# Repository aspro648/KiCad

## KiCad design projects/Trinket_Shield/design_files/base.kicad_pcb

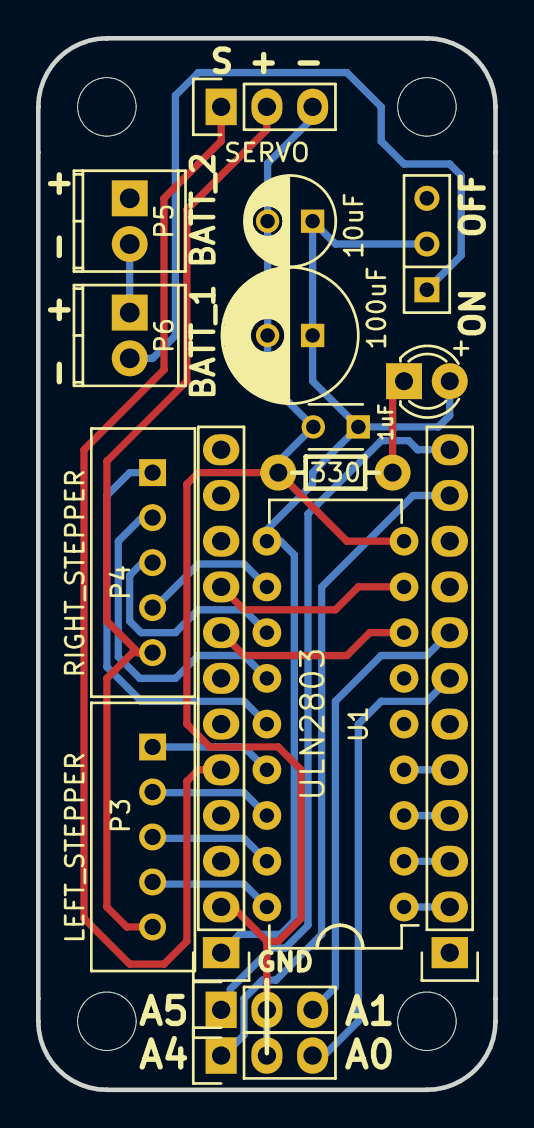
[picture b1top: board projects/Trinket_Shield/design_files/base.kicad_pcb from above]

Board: 2 copper layers, 25.4 x 58.4 mm, 22 parts (0 on the bottom side), 25 nets.

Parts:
C1: 100uF; C_Radial_D7.5_L11.2_P2.5
C2: 10uF; C_Radial_D5_L11_P2.5
C3: 1uF; C_Disc_D3_P2.5
D1: LED; LED-3MM
P1: TRINKET_LEFT; Pin_Header_Straight_1x12
P2: TRINKET_RIGHT; Pin_Header_Straight_1x12
P3: LEFT_STEPPER; JST_B5B-XH-A
P4: RIGHT_STEPPER; JST_B5B-XH-A
P5: BATT1; TerminalBlock_Pheonix_MPT-2.54mm_2pol
P6: BATT2; TerminalBlock_Pheonix_MPT-2.54mm_2pol
P7: SERVO; Pin_Header_Straight_1x03
P8: A5 - A1; Pin_Header_Straight_1x03
P9, P9#2, P9#3, P9#4: CONN_01X01; Lego_Pad
P11: A4 - A0; Pin_Header_Straight_1x03
R1: 330; Resistor_Horz
SW1: SPST; SW_Micro_SPST
U1: ULN2803; DIP-18_W7.62mm
VAL: MadeInOregonRev25
VAL#2: MB225rev

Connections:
/A0: P1.7, P11.3
/A1: P1.8, P8.3
/A4: P1.11, P11.1
/A5: P1.12, P8.1
/D3: P2.9, U1.8
/D4: P2.8, U1.7
/D8: P2.5, P7.1
/D10: P1.2, U1.1
/D11: P1.3, U1.2
/D12: P1.4, U1.3
/D13: P1.5, U1.4
/VBAT: C1.1, C2.1, C3.1, D1.2, P2.1, SW1.2, U1.10
GND: C1.2, C2.2, C3.2, P2.2, P7.3, P8.2, P11.2, R1.2, U1.9
unnamed: D1.1, R1.1
unnamed: P3.1, U1.15
unnamed: P3.2, U1.16
unnamed: P3.3, U1.17
unnamed: P3.4, U1.18
unnamed: P3.5, P4.5, P7.2
unnamed: P4.1, U1.14
unnamed: P4.2, U1.13
unnamed: P4.3, U1.12
unnamed: P4.4, U1.11
unnamed: P5.2, P6.1
unnamed: P6.2, SW1.1

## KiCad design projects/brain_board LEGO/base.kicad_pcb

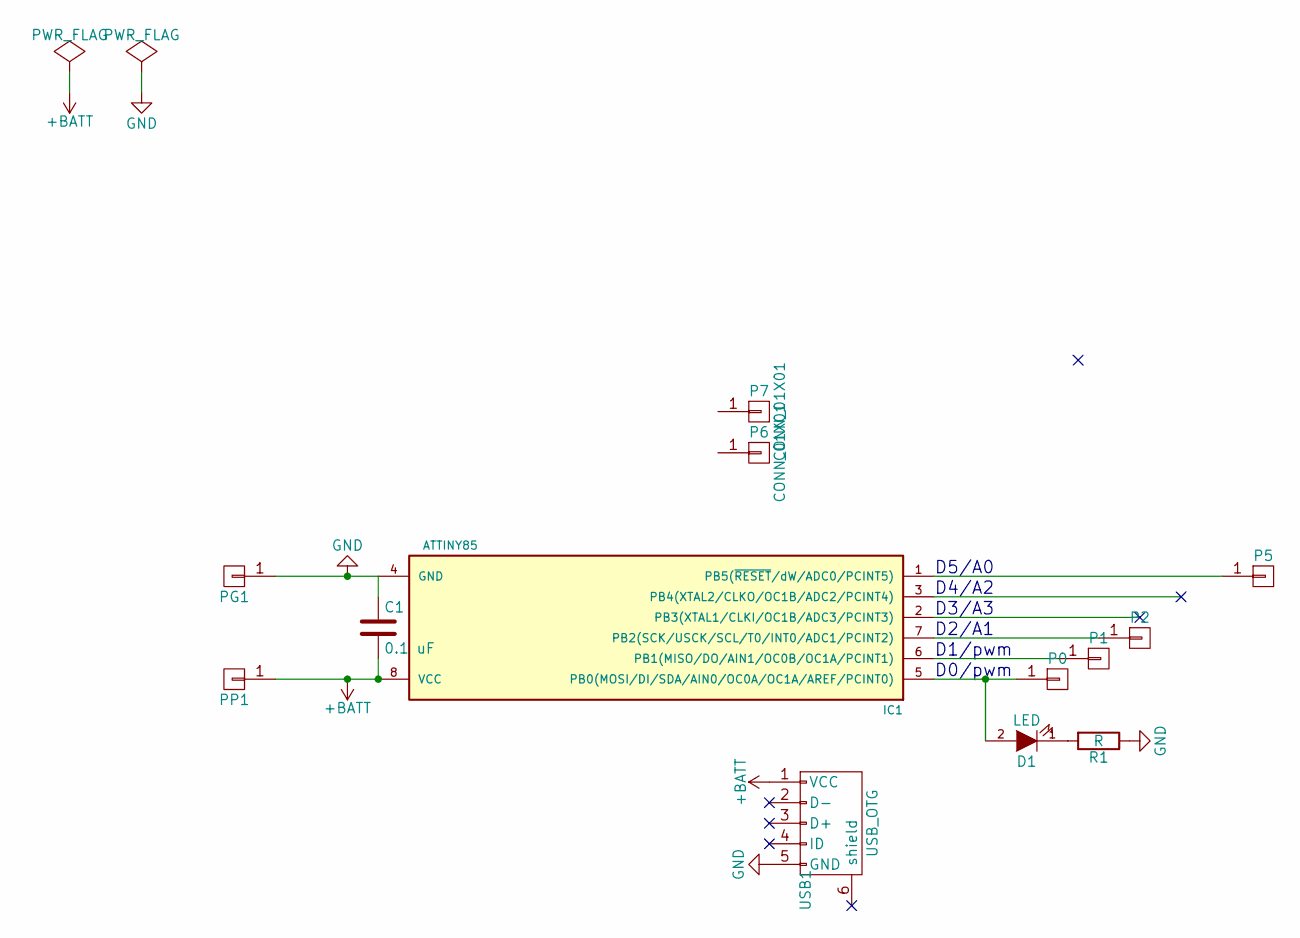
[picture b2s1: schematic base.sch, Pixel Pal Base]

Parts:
C1: 0.1 uF; C_0805
D1: LED; LED-0805
IC1: ATTINY85; SOIC-8-N
P0, P1, P2, P5: CONN_01X01; Lego_Pad
P6, P7: CONN_01X01; Lego_Drill
PG1: CONN_01X01; Lego_Pad
PP1: CONN_01X01; Lego_Pad
R1: R; R_0805
USB1: USB_OTG; USB_Micro-B

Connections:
+BATT: C1.2, IC1.8 (VCC), PP1.1, USB1.1 (VCC)
GND: C1.1, IC1.4 (GND), PG1.1, R1.1, USB1.5 (GND)
unnamed: D1.1 (K), R1.2
unnamed: D1.2 (A), IC1.5 (PB0(MOSI/DI/SDA/AIN0/OC0A/OC1A/AREF/PCI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), P0.1
unnamed: IC1.1 (PB5(~RESET~/dW/ADC0/PCINT5)), P5.1
unnamed: IC1.6 (PB1(MISO/DO/AIN1/OC0B/OC1A/PCINT1)), P1.1
unnamed: IC1.7 (PB2(SCK/USCK/SCL/T0/INT0/ADC1/PCINT2)), P2.1

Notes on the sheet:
D5/A0
D4/A2
D3/A3
D2/A1
D1/pwm
D0/pwm

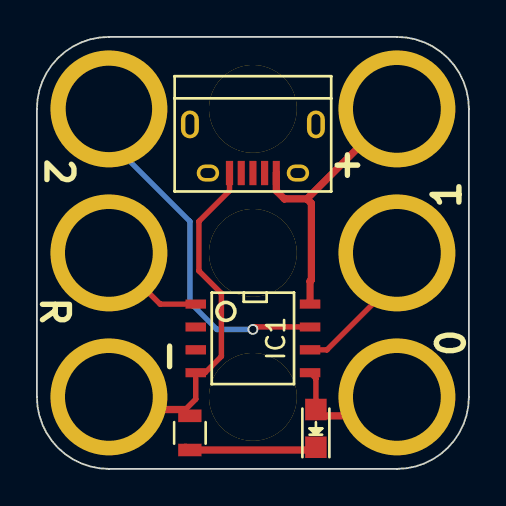
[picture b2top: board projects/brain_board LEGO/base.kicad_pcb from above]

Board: 2 copper layers, 24.0 x 24.0 mm, 13 parts (0 on the bottom side), 7 nets.

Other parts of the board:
P6#2: CONN_01X01; Lego_Drill

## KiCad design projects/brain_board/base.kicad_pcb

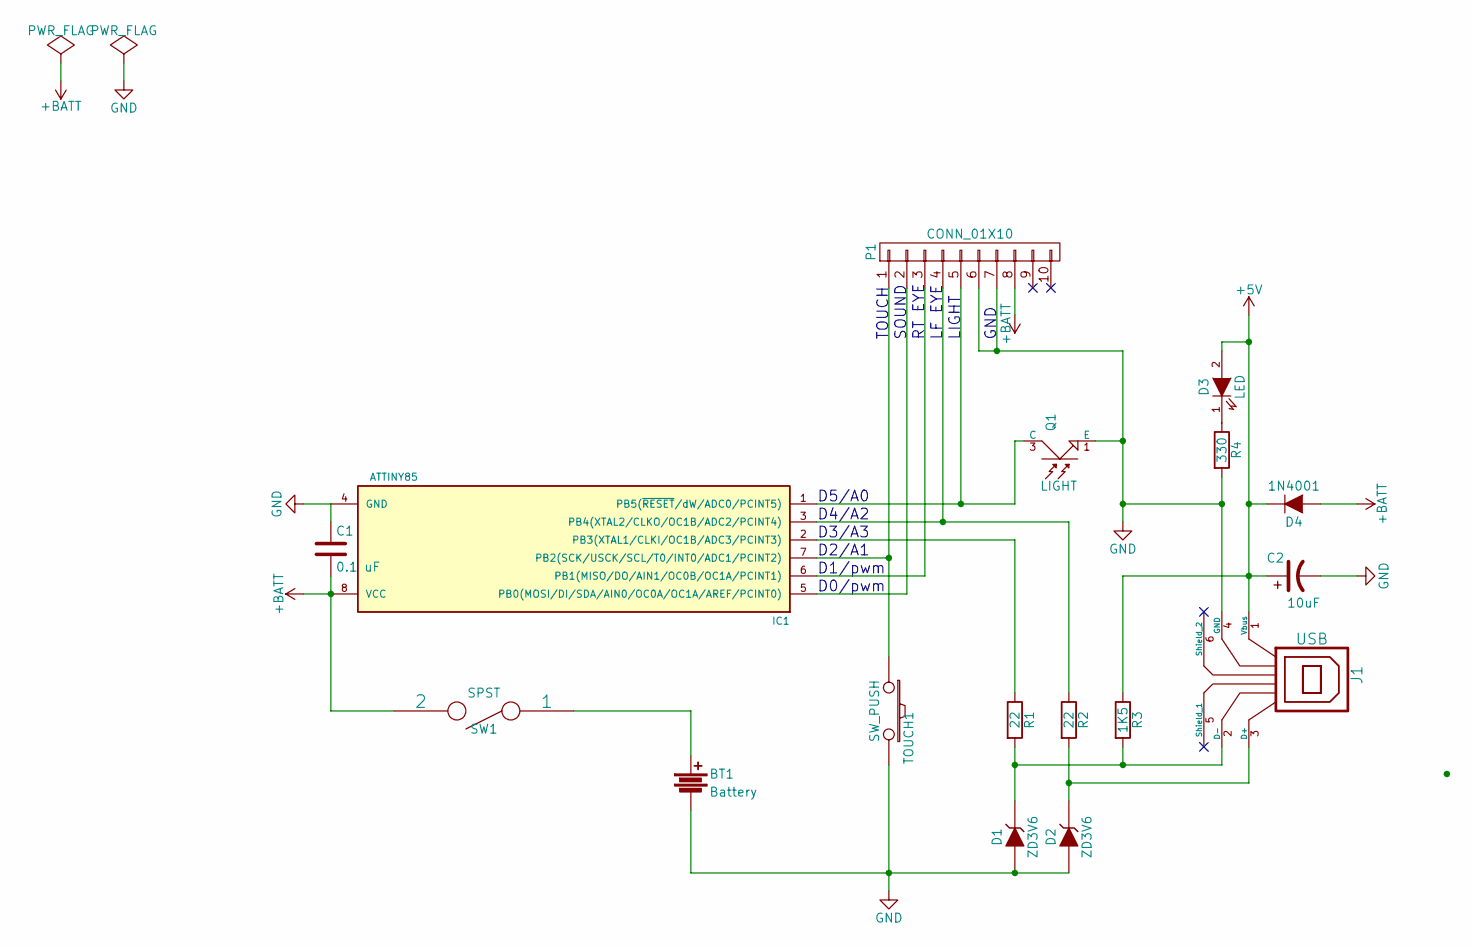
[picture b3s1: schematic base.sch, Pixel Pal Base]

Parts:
BT1: Battery; BATT_CR2032
C1: 0.1 uF; C1
C2: 10uF; C_Radial_D6.3_L11.2_P2.5
D1, D2: ZD3V6; D3
D3: LED; LED-5MM
D4: 1N4001; Diode_DO-41_SOD81_Horizontal_RM10
IC1: ATTINY85; DIP-8__300
J1: USB; USB_B
P1: CONN_01X10; Pin_Header_Straight_1x10
Q1: LIGHT; PHOTO_TRANS
R1, R2: 22; Resistor_Horizontal_RM10mm
R3: 1K5; Resistor_Horizontal_RM10mm
R4: 330; Resistor_Horizontal_RM10mm
SW1: SPST; SW_SPST
TOUCH1: SW_PUSH; SW_PUSH_TOUCH

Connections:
+5V: C2.1, D3.2 (A), D4.2 (K), J1.1 (Vbus), R3.1
+BATT: C1.2, D4.1 (A), IC1.8 (VCC), P1.8, SW1.2
GND: BT1.2, C1.1, C2.2, D1.1 (A), D2.1 (A), IC1.4 (GND), J1.4 (GND), P1.6, P1.7, Q1.1 (E), R4.2, TOUCH1.2
unnamed: BT1.1, SW1.1
unnamed: D1.2 (K), J1.2 (D-), R1.2, R3.2
unnamed: D2.2 (K), J1.3 (D+), R2.2
unnamed: D3.1 (K), R4.1
unnamed: IC1.1 (PB5(~RESET~/dW/ADC0/PCINT5)), P1.5, Q1.3 (C)
unnamed: IC1.2 (PB3(XTAL1/CLKI/OC1B/ADC3/PCINT3)), R1.1
unnamed: IC1.3 (PB4(XTAL2/CLKO/OC1B/ADC2/PCINT4)), P1.4, R2.1
unnamed: IC1.5 (PB0(MOSI/DI/SDA/AIN0/OC0A/OC1A/AREF/PCI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), P1.2
unnamed: IC1.6 (PB1(MISO/DO/AIN1/OC0B/OC1A/PCINT1)), P1.3
unnamed: IC1.7 (PB2(SCK/USCK/SCL/T0/INT0/ADC1/PCINT2)), P1.1, TOUCH1.1

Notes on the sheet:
D5/A0
D4/A2
D3/A3
D2/A1
D1/pwm
D0/pwm
TOUCH
SOUND
RT EYE
LF EYE
GND
LIGHT

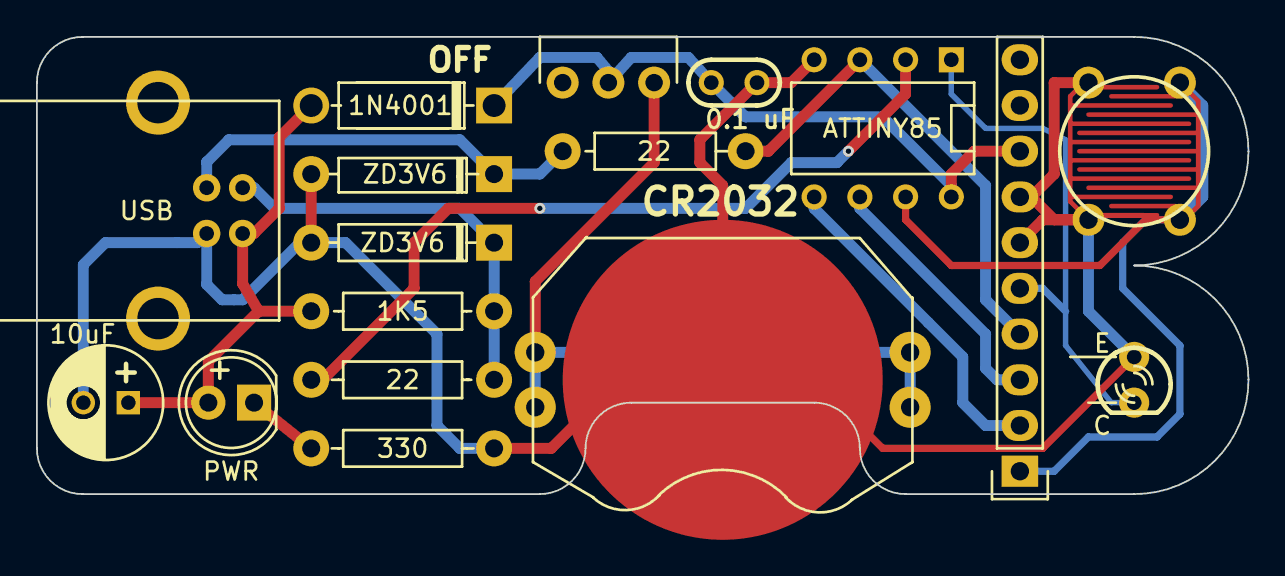
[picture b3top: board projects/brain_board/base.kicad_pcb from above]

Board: 2 copper layers, 67.3 x 25.4 mm, 17 parts (0 on the bottom side), 13 nets.

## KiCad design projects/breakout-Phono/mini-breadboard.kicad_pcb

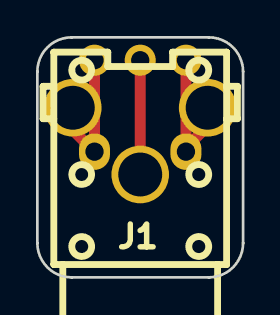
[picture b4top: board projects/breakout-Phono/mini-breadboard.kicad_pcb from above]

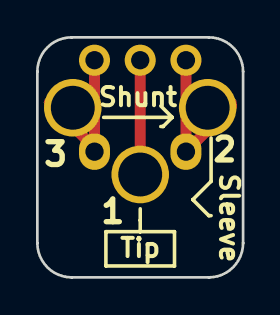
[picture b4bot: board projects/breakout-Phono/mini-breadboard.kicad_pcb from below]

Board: 2 copper layers, 11.4 x 13.3 mm, 3 parts (2 on the bottom side), 3 nets.

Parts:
J1: JACK_2P; rca_yellow
P1, P2: CONN_01X03; Pin_Header_Straight_1x03

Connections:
unnamed: J1.1, P1.1, P2.1
unnamed: J1.2, P1.2
unnamed: J1.3, P1.3, P2.3

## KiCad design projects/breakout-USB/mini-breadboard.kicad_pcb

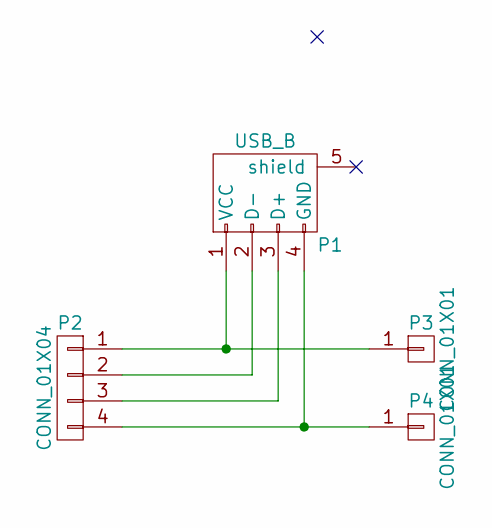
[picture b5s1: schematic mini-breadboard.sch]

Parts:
P1: USB_B
P2: CONN_01X04; Pin_Header_Straight_1x04
P3, P4: CONN_01X01; Pin_Header_Straight_1x01

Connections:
unnamed: P1.1 (VCC), P2.1, P3.1
unnamed: P1.2 (D-), P2.2
unnamed: P1.3 (D+), P2.3
unnamed: P1.4 (GND), P2.4, P4.1

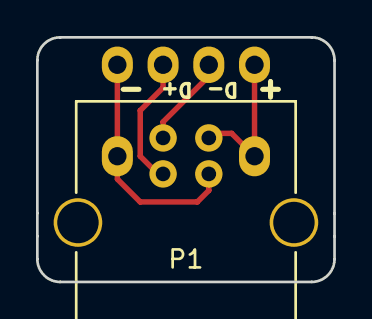
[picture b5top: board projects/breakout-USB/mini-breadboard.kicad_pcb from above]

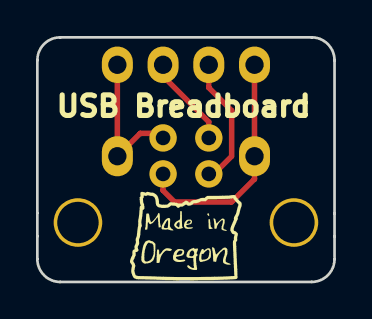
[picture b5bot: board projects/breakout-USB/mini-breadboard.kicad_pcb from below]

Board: 2 copper layers, 16.5 x 13.6 mm, 5 parts (3 on the bottom side), 4 nets.

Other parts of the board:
VAL: MadeInOregonRev25

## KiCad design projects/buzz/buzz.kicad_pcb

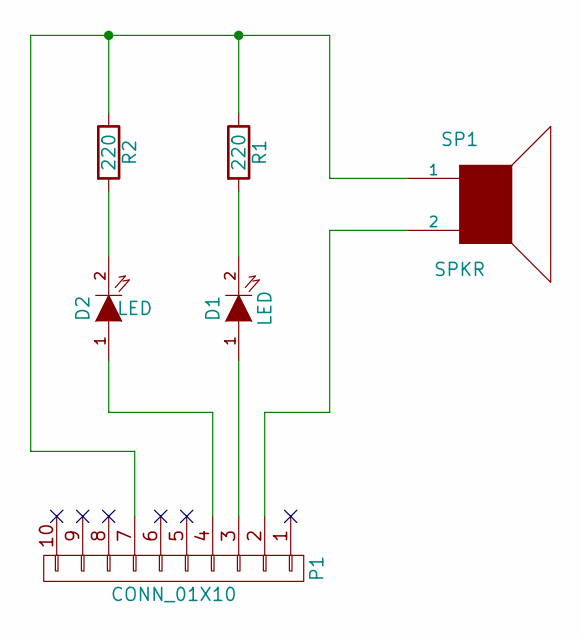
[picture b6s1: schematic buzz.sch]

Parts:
D1, D2: LED; LED_10MM
P1: CONN_01X10; Pin_Header_Straight_1x10
R1, R2: 220; Resistor_Horizontal_RM10mm
SP1: SPKR; PS1240_piezo

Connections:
unnamed: D1.1 (A), P1.3
unnamed: D1.2 (K), R1.2
unnamed: D2.1 (A), P1.4
unnamed: D2.2 (K), R2.2
unnamed: P1.2, SP1.2
unnamed: P1.7, R1.1, R2.1, SP1.1

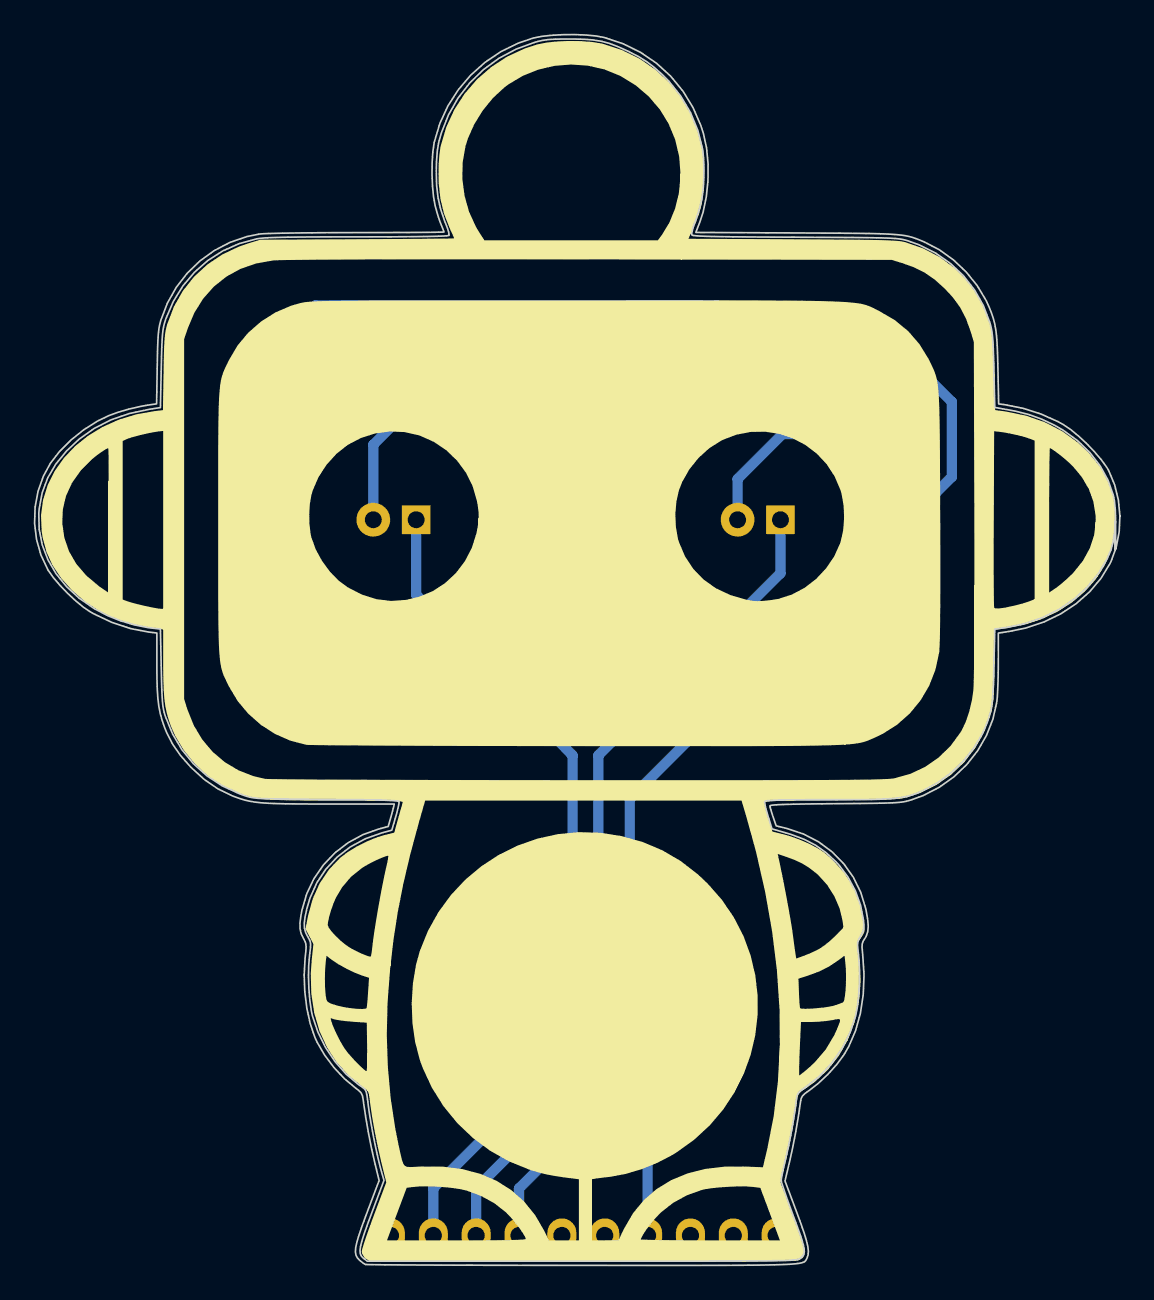
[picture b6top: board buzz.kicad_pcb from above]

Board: 2 copper layers, 64.3 x 72.9 mm, 6 parts (0 on the bottom side), 6 nets.

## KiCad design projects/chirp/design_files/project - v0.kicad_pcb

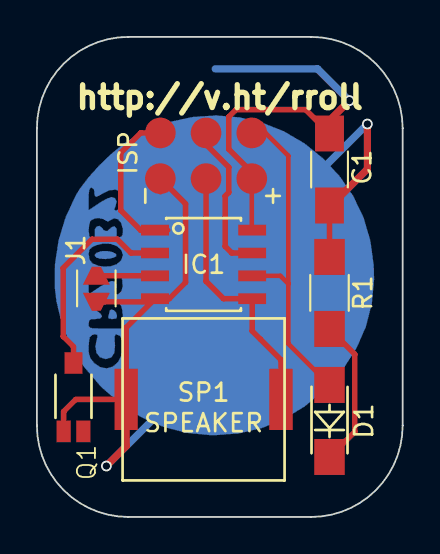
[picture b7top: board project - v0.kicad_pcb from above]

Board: 2 copper layers, 20.3 x 26.7 mm, 9 parts (1 on the bottom side), 9 nets.

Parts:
BT1: Battery; BATT_CR2032_SMD
C1: 0.1 uF; C_1206_HandSoldering
CON1: ISP; Pin_Header_Straight_2x03_Pitch2.54mm
D1: LED; LED_1206_HandSoldering
IC1: ATTINY85; SOIC-8_3.9x4.9mm_Pitch1.27mm
J1: JMP; R_1206_HandSoldering
Q1: LIGHT; PHOTO_TRANS
R1: 330; R_1206_HandSoldering
SP1: SPEAKER; PS1240_piezo

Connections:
+BATT: BT1.1, C1.2, CON1.2, IC1.8
GND: BT1.2, C1.1, CON1.6, IC1.4, J1.1, Q1.1, R1.1, SP1.1
unnamed: CON1.1, D1.2, IC1.6
unnamed: CON1.3, IC1.7
unnamed: CON1.4, IC1.5, SP1.2
unnamed: CON1.5, IC1.1
unnamed: D1.1, R1.2
unnamed: IC1.2, Q1.3
unnamed: IC1.3, J1.2

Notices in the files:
projects/brain_board/base.kicad_pcb:
R1.0  CC BY-NC 3.0
